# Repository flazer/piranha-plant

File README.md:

# Remote controlled "Mario piranha plant"

## Introduction
This project was realized while streaming live at [https://www.twitch.tv/chrisfigge](https://www.twitch.tv/chrisfigge).
I got this piranha plant as a christmas-gift but I think it's much cooler to use it as a remote controlled gadget while streaming.
So I wrote a lot of code, printed a lot of stuff and did this electronic-thingie.
But this time with a lot of help from the mighty community.
[0FR0](https://github.com/0FR0) tried to teach me KiCad and developed my first PCB ever.
Many, many thanks, dude! Awesome job!

So you'll find everything you need to build your own remote controlled plant in here:

- BOM (everything you've to buy)
- STL files (everything to print)
- images (everything you need to watch)
- code (everything to controll your plant via wifi)
- schematics (everything to build your own circuit)

## BOM
- 1x Wemos D1 mini: [https://amzn.to/389YZPE](https://amzn.to/389YZPE) *
- 1x Nema17 Pancake: [https://amzn.to/3bYEyGN](https://amzn.to/3bYEyGN) *
- 2x 10kOhm Resistors: [https://amzn.to/3sRnLwe](https://amzn.to/3sRnLwe) *
- 1x TMC2208 (Stepperdriver): [https://amzn.to/2PzTYd1](https://amzn.to/2PzTYd1) *
- 1x IRFZ44N (Mosfet): [https://amzn.to/3kILgEA](https://amzn.to/3kILgEA) *
- 1x LM2596 (Stepdown module): [https://amzn.to/38aoLn4](https://amzn.to/38aoLn4) *
- 1x Microswitch [https://amzn.to/3rUtHEC](https://amzn.to/3rUtHEC) *
- 1x DC-Plug [https://amzn.to/3rSaIKy](https://amzn.to/3rSaIKy) *

Links marked with an asterisk (*) are affiliates. This means if you order these items via amazon, i'll get a very small piece of this (financial) cake. You'll not pay more (not even 1 cent. literally nothing). And I can reinvest the money for new ideas and projects. From the community for the community. :)

## PCB
The pcb shown in "images" are an old previous version and differs from the current state. But works exactly the same.

## Enclosure  
If you want to print the case I've used please take a look into the "stls"-folder.  
The files are named as what they are used for.
To get a better understanding, please watch the images, stored in the "images"-folder.

## Assembly
To assemble the 3d printed parts. You will need some glue, to glue the inlay parts.
Because I'm not very good in get parts in correct position, I've printed a centering guide.
Just place the guide onto the platform and glue the "hill" nearly perfectly centered onto the baseplate. Remove the guide afterwards.

## Twitch

If you are interested in what I'm doing, just have a look at twitch:
[https://www.twitch.tv/chrisfigge](https://www.twitch.tv/chrisfigge)

## Tip
I am doing all this stuff in my freetime. And, oh boy, these projects take a lot of time. I swear.
If you want to support my work feel free to cheer some bits or giftsubs on my [Twitch channel](https://www.twitch.tv/chrisfigge) or you can always leave some tip via [paypal](https://paypal.me/flazer). Thanks a lot!

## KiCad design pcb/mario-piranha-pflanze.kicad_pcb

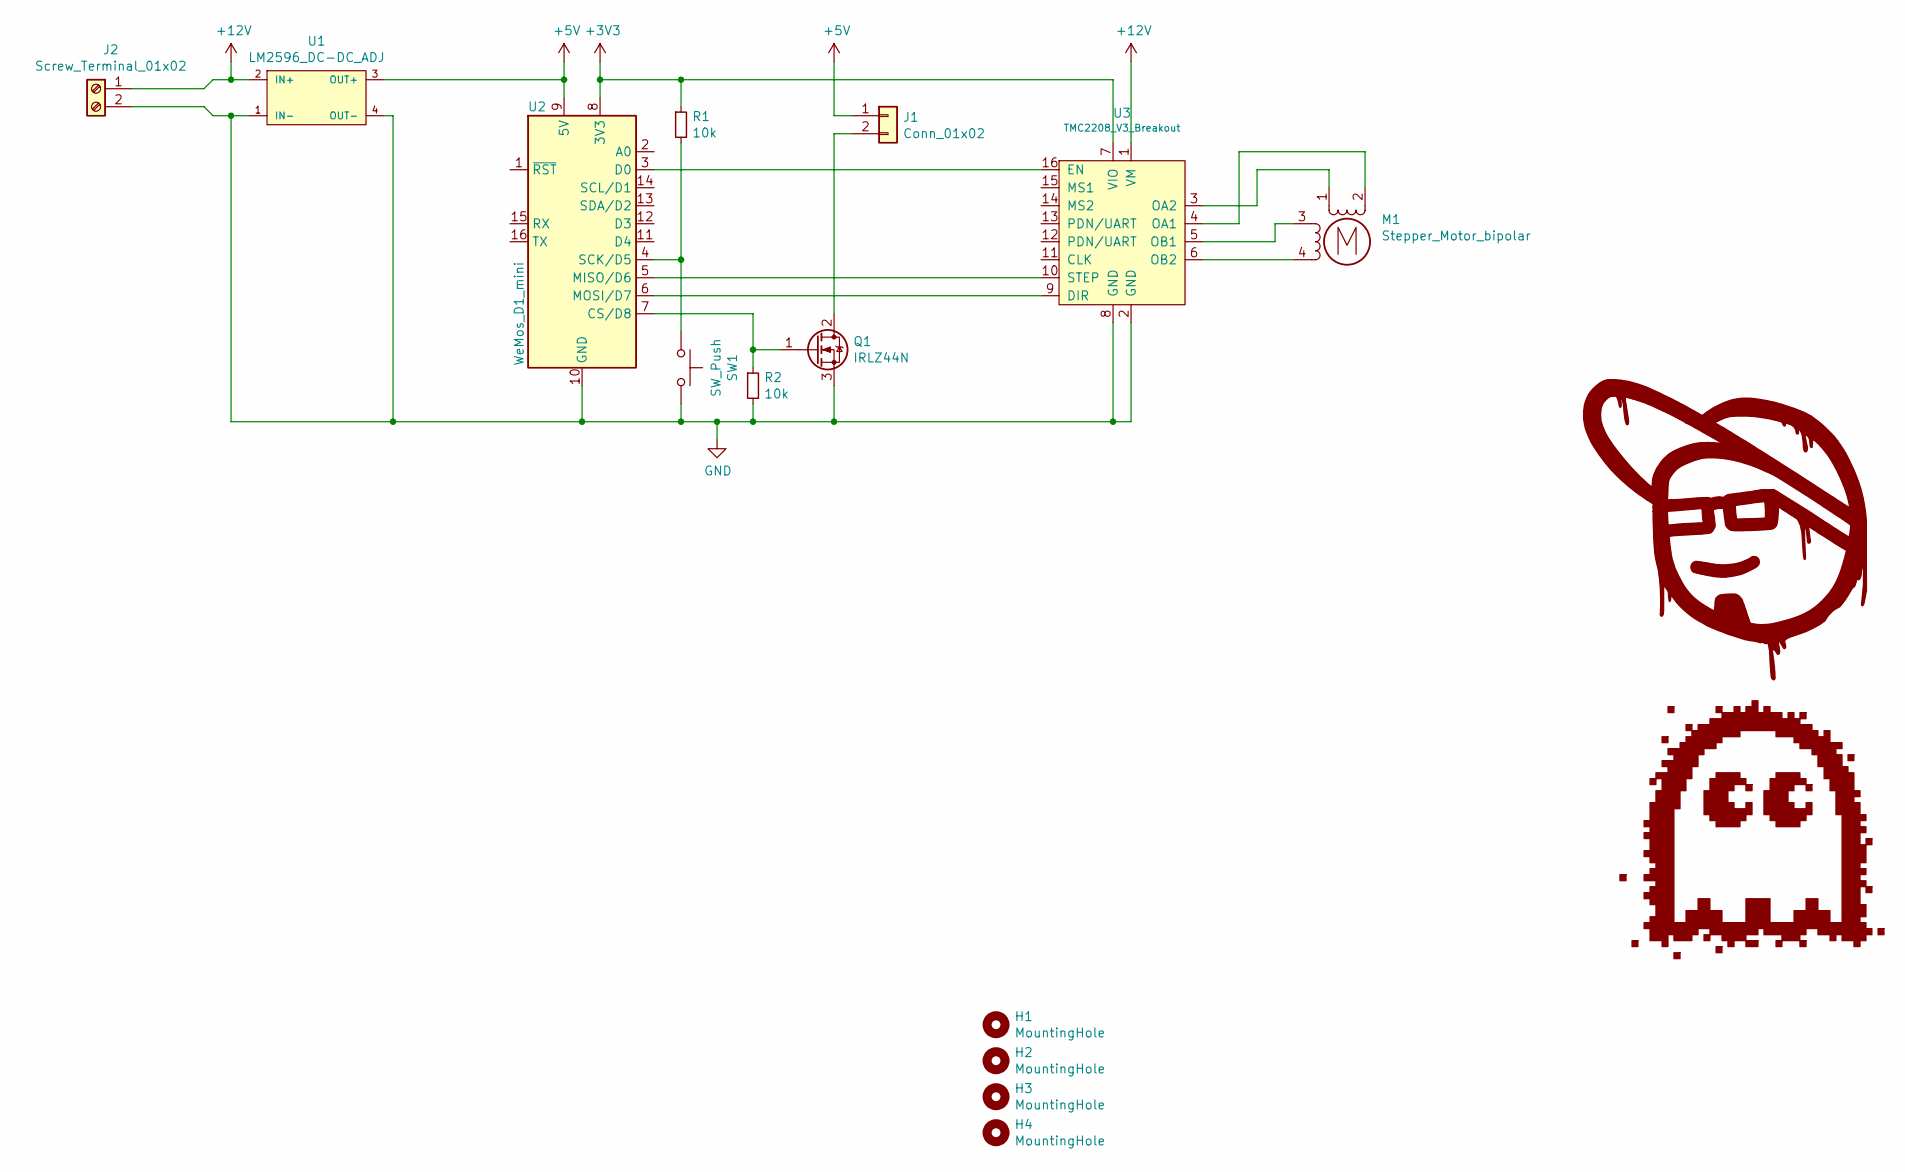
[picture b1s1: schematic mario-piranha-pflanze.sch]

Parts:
G1: figge_LOGO; figge_logo_15x15,9
G2: fritte_LOGO; fritte_LOGO_5x5
H1, H2, H3, H4: MountingHole; MountingHole_3.2mm_M3
J1: Conn_01x02; PinSocket_1x02_P2.54mm_Vertical
J2: Screw_Terminal_01x02; TerminalBlock_bornier-2_P5.08mm
M1: Stepper_Motor_bipolar; PinSocket_1x04_P2.54mm_Vertical
Q1: IRLZ44N; TO-220-3_Vertical
R1, R2: 10k; R_Axial_DIN0207_L6.3mm_D2.5mm_P10.16mm_Horizontal
SW1: SW_Push; PinSocket_1x02_P2.54mm_Vertical
U1: LM2596_DC-DC_ADJ; LM2596_DC-DC
U2: WeMos_D1_mini; WEMOS_D1_mini_light
U3: TMC2208_V3_Breakout

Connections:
+3V3: R1.1, U2.8 (3V3), U3.7 (VIO)
+5V: J1.1, U1.3 (OUT+), U2.9 (5V)
+12V: J2.1, U1.2 (IN+), U3.1 (VM)
GND: J2.2, Q1.3 (S), R2.2, SW1.2, U1.1 (IN-), U1.4 (OUT-), U2.10 (GND), U3.2 (GND), U3.8 (GND)
unnamed: J1.2, Q1.2 (D)
unnamed: M1.1, U3.3 (OA2)
unnamed: M1.2 (-), U3.4 (OA1)
unnamed: M1.3, U3.5 (OB1)
unnamed: M1.4, U3.6 (OB2)
unnamed: Q1.1 (G), R2.1, U2.7 (CS/D8)
unnamed: R1.2, SW1.1, U2.4 (SCK/D5)
unnamed: U2.3 (D0), U3.16 (EN)
unnamed: U2.5 (MISO/D6), U3.10 (STEP)
unnamed: U2.6 (MOSI/D7), U3.9 (DIR)

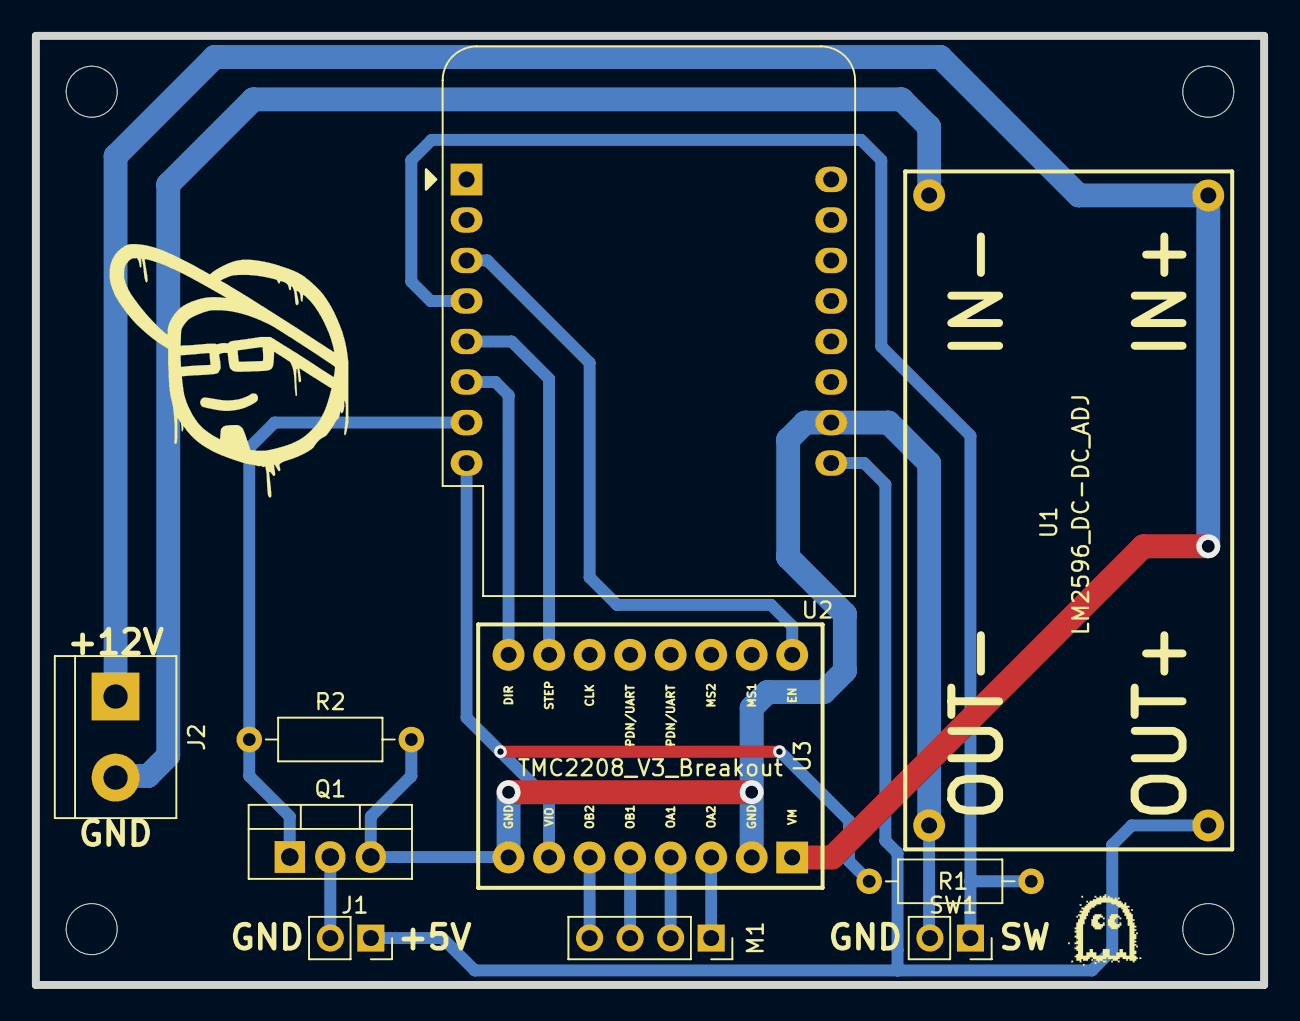
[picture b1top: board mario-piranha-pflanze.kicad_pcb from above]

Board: 2 copper layers, 77.0 x 59.5 mm, 16 parts (0 on the bottom side), 14 nets.

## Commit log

2021-03-04 initial
2021-03-04 adding Readme
2021-03-15 updating
2021-03-15 added photos
2021-03-15 adding pcb, layout and scheme by 0fr0
2021-03-15 adding lib information
2021-03-15 tinify the images
